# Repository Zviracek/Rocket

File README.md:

# Rocket
This repository contains everything needed for succesfull model-scale rocket flight. Or it should once it's done.

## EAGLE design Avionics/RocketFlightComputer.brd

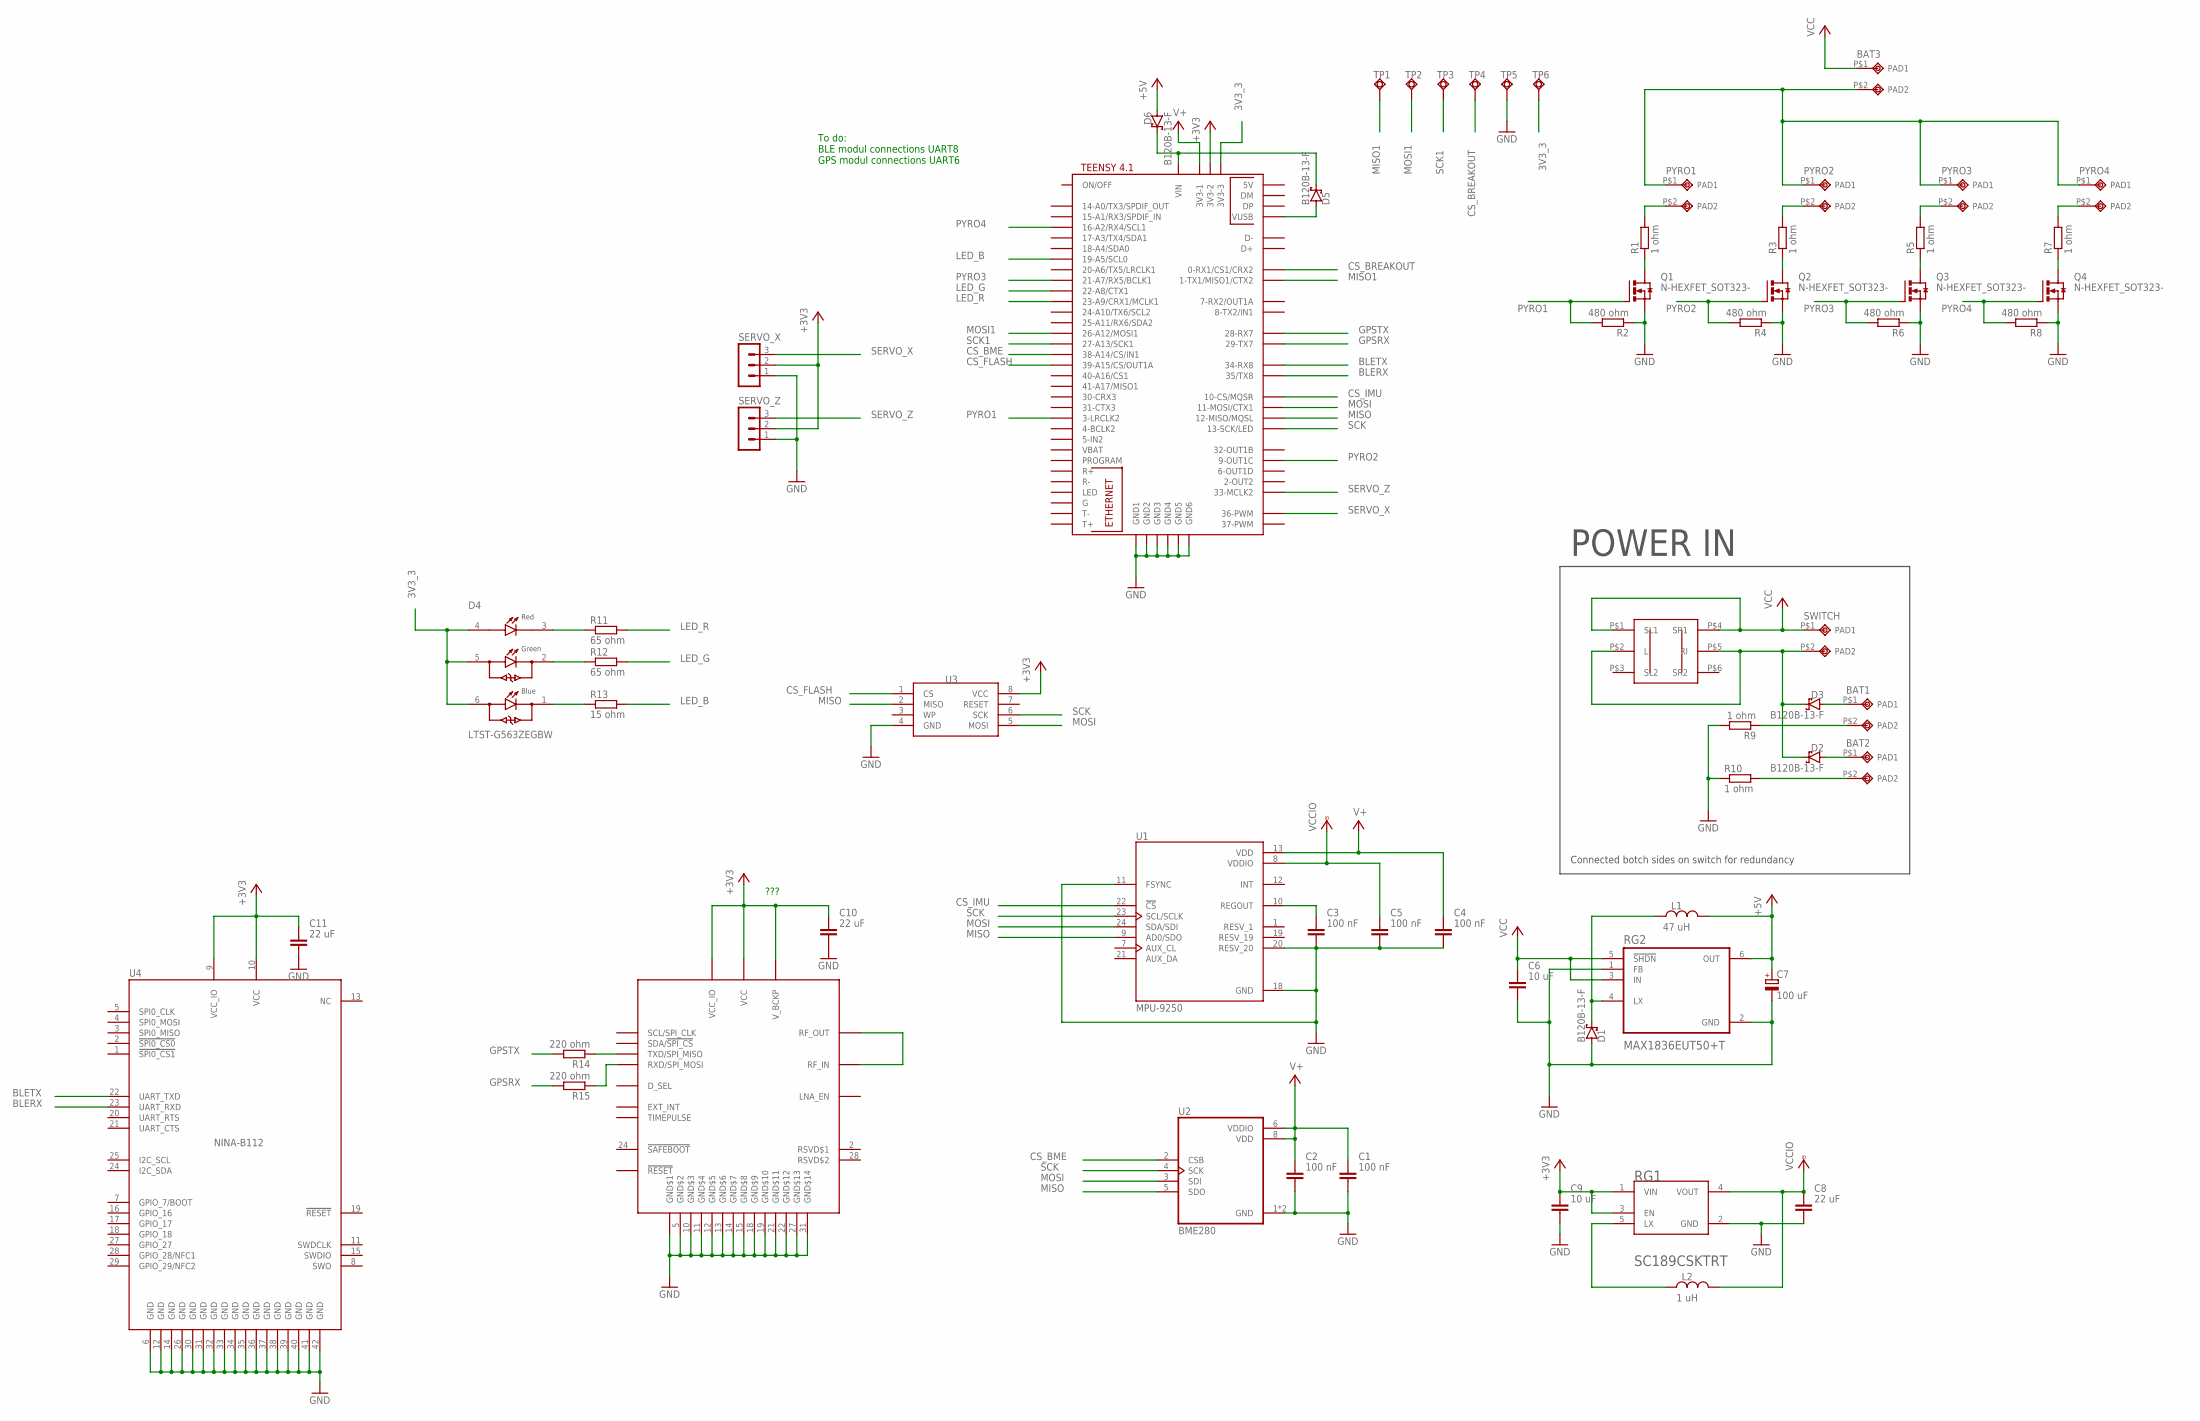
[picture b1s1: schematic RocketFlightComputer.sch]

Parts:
BAT1, BAT2, BAT3: 2PINPAD
C1, C2, C3, C4, C5: 100 nF; CAPC3216X135
C6, C9: 10 uF; CAPC3216X135
C7: 100 uF; B/3528-21W
C8, C10, C11: 22 uF; CAPC3216X135
D1, D2, D3, D5, D6: B120B-13-F; SMB
D4: LTST-G563ZEGBW; LED_LTST-G563ZEGBW
L1: 47 uH; INDM3225X240
L2: 1 uH; CAPC2012X110
PYRO1, PYRO2, PYRO3, PYRO4: 2PINPAD
Q1, Q2, Q3, Q4: N-HEXFET_SOT323-; SOT223
R1, R3, R5, R7, R9, R10: 1 ohm; R1206
R2, R4, R6, R8: 480 ohm; R1206
R11, R12: 65 ohm; R1206
R13: 15 ohm; R1206
R14, R15: 220 ohm; R1206
RG1: SEMTECH_SC189CSKTRTSEMTECH_SC189CSKTRT_0_0; SEMTECH_SC189CSKTRT_0
RG2: MAX1836EUT50+T; SOT95P280X145-6N
SERVO_X: MA03-1
SERVO_Z: MA03-1
SWITCH: 2PINPAD
TP1, TP2, TP3, TP4, TP5, TP6: TPSQTP13SQ; TP13SQ
U1: MPU-9250; QFN40P300X300X105-24N
U2: BME280; PSON65P250X250X100-8N
U3: FLASHSOIC8; SOIC127P600X175-8N
U4: NINA-B112; NINA112-42
U$1: TEENSY41
U$2: CAM-M8
U$3: DUAL_SW; DUAL_SWITCH

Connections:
3V3_3: D4.4, D4.5, D4.6, TP6.TP, U$1.3V3-3
+3V3: C9.1, C10.1, C11.1, RG1.1 (VIN), RG1.3 (EN), SERVO_X.2, SERVO_Z.2, U3.8 (VCC), U4.9 (VCC_IO), U4.10 (VCC), U$1.3V3-2, U$2.1 (VCC_IO), U$2.8 (V_BCKP), U$2.9 (VCC)
+5V: C7.+, D6.P$2 (A), L1.2, RG2.6 (OUT)
BLERX: U4.23 (UART_RXD), U$1.35-TX8 (35/TX8)
BLETX: U4.22 (UART_TXD), U$1.34-RX8
CS_BME: U2.2 (CSB), U$1.38-A14/CS/IN1
CS_BREAKOUT: TP4.TP, U$1.0-RX1/CS1/CRX2
CS_FLASH: U3.1 (CS), U$1.39-A15/CS/OUT1A
CS_IMU: U1.22 (!CS), U$1.10-CS\MQSR (10-CS/MQSR)
GND: C1.2, C2.2, C3.2, C4.2, C5.2, C6.2, C7.-, C8.2, C9.2, C10.2, C11.2, D1.P$2 (A), Q1.3 (S), Q2.3 (S), Q3.3 (S), Q4.3 (S), R2.1, R4.1, R6.1, R8.1, R9.2, R10.1, RG1.2 (GND), RG2.1 (FB), RG2.2 (GND), SERVO_X.1, SERVO_Z.1, TP5.TP, U1.11 (FSYNC), U1.18 (GND), U1.20 (RESV_20), U2.1 (GND), U2.7 (GND), U3.4 (GND), U4.6 (GND), U4.12 (GND), U4.14 (GND), U4.26 (GND), U4.30 (GND), U4.31 (GND), U4.32 (GND), U4.33 (GND), U4.34 (GND), U4.35 (GND), U4.36 (GND), U4.37 (GND), U4.38 (GND), U4.39 (GND), U4.40 (GND), U4.41 (GND), U4.42 (GND), U$1.GND1, U$1.GND2, U$1.GND3, U$1.GND4, U$1.GND5, U$1.GND6, U$2.4 (GND$1), U$2.5 (GND$2), U$2.10 (GND$3), U$2.11 (GND$4), U$2.12 (GND$5), U$2.13 (GND$6), U$2.14 (GND$7), U$2.15 (GND$8), U$2.18 (GND$9), U$2.19 (GND$10), U$2.21 (GND$11), U$2.22 (GND$12), U$2.27 (GND$13), U$2.31 (GND$14)
GPSRX: R15.2, U$1.29-TX7
GPSTX: R14.2, U$1.28-RX7
LED_B: R13.2, U$1.19-A5/SCL0
LED_G: R12.2, U$1.22-A8/CTX1
LED_R: R11.2, U$1.23-A9/CRX1/MCLK1
MISO: U1.9 (AD0/SDO), U2.5 (SDO), U3.2 (MISO), U$1.12-MISO/MQSL
MISO1: TP1.TP, U$1.1-TX1/MISO1/CTX2
MOSI: U1.24 (SDA/SDI), U2.3 (SDI), U3.5 (MOSI), U$1.11-MOSI/CTX1
MOSI1: TP2.TP, U$1.26-A12/MOSI1
unnamed: C3.1, U1.10 (REGOUT)
unnamed: D5.P$1 (B), D6.P$1 (B), U$1.VIN
unnamed: Q1.4 (D), R1.1
unnamed: PYRO1.P$2 (PAD2), R1.2
unnamed: Q2.4 (D), R3.1
unnamed: PYRO2.P$2 (PAD2), R3.2
unnamed: D2.P$1 (B), D3.P$1 (B), SWITCH.P$2 (PAD2), U$3.P$2 (LI), U$3.P$5 (RI)
unnamed: D4.3, R11.1
unnamed: Q3.4 (D), R5.1
unnamed: PYRO3.P$2 (PAD2), R5.2
unnamed: D4.2, R12.1
unnamed: Q4.4 (D), R7.1
unnamed: PYRO4.P$2 (PAD2), R7.2
unnamed: BAT1.P$2 (PAD2), R9.1
unnamed: BAT2.P$2 (PAD2), R10.2
unnamed: D4.1, R13.1
unnamed: D1.P$1 (B), L1.1, RG2.4 (LX)
unnamed: BAT2.P$1 (PAD1), D2.P$2 (A)
unnamed: BAT1.P$1 (PAD1), D3.P$2 (A)
unnamed: D5.P$2 (A), U$1.VUSB
unnamed: U$2.16 (RF_OUT), U$2.17 (RF_IN)
unnamed: L2.1, RG1.5 (LX)
unnamed: BAT3.P$2 (PAD2), PYRO1.P$1 (PAD1), PYRO2.P$1 (PAD1), PYRO3.P$1 (PAD1), PYRO4.P$1 (PAD1)
unnamed: R14.1, U$2.25 (TXD/SPI_MISO)
unnamed: R15.1, U$2.26 (RXD/SPI_MOSI)
PYRO1: Q1.1 (G), R2.2, U$1.3-LRCLK2
PYRO2: Q2.1 (G), R4.2, U$1.9-OUT1C
PYRO3: Q3.1 (G), R6.2, U$1.21-A7/RX5/BCLK1
PYRO4: Q4.1 (G), R8.2, U$1.16-A2/RX4/SCL1
SCK: U1.23 (SCL/SCLK), U2.4 (SCK), U3.6 (SCK), U$1.13-SCK/LED
SCK1: TP3.TP, U$1.27-A13/SCK1
SERVO_X: SERVO_X.3, U$1.36-PWM
SERVO_Z: SERVO_Z.3, U$1.33-MCLK2
V+: C1.1, C2.1, C4.1, U1.13 (VDD), U2.6 (VDDIO), U2.8 (VDD), U$1.3V3-1
VCC: BAT3.P$1 (PAD1), C6.1, RG2.3 (IN), RG2.5 (!SHDN), SWITCH.P$1 (PAD1), U$3.P$1 (SL1), U$3.P$4 (SR1)
VCCIO: C5.1, C8.1, L2.2, RG1.4 (VOUT), U1.8 (VDDIO)

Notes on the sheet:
Connected botch sides on switch for redundancy
POWER IN
To do: BLE modul connections UART8 GPS modul connections UART6
???

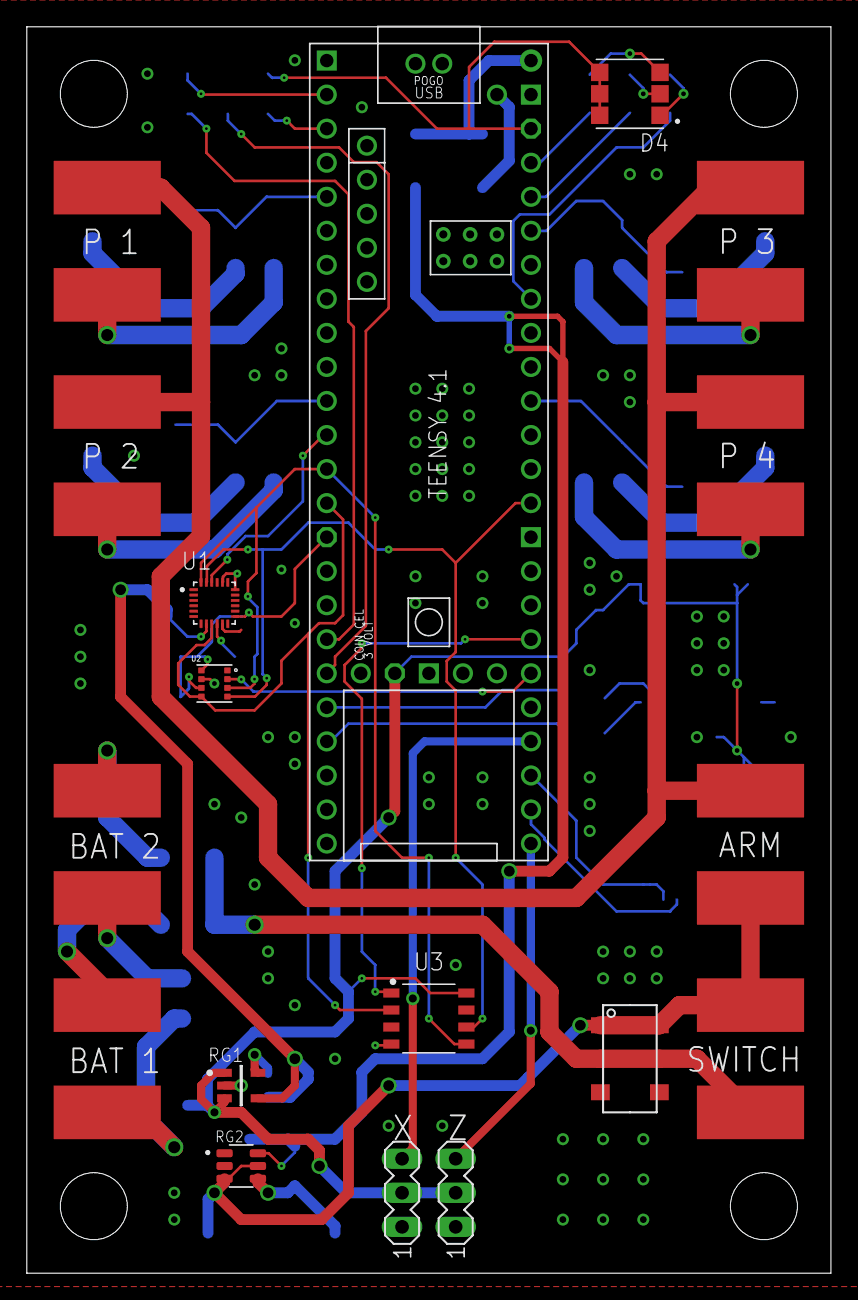
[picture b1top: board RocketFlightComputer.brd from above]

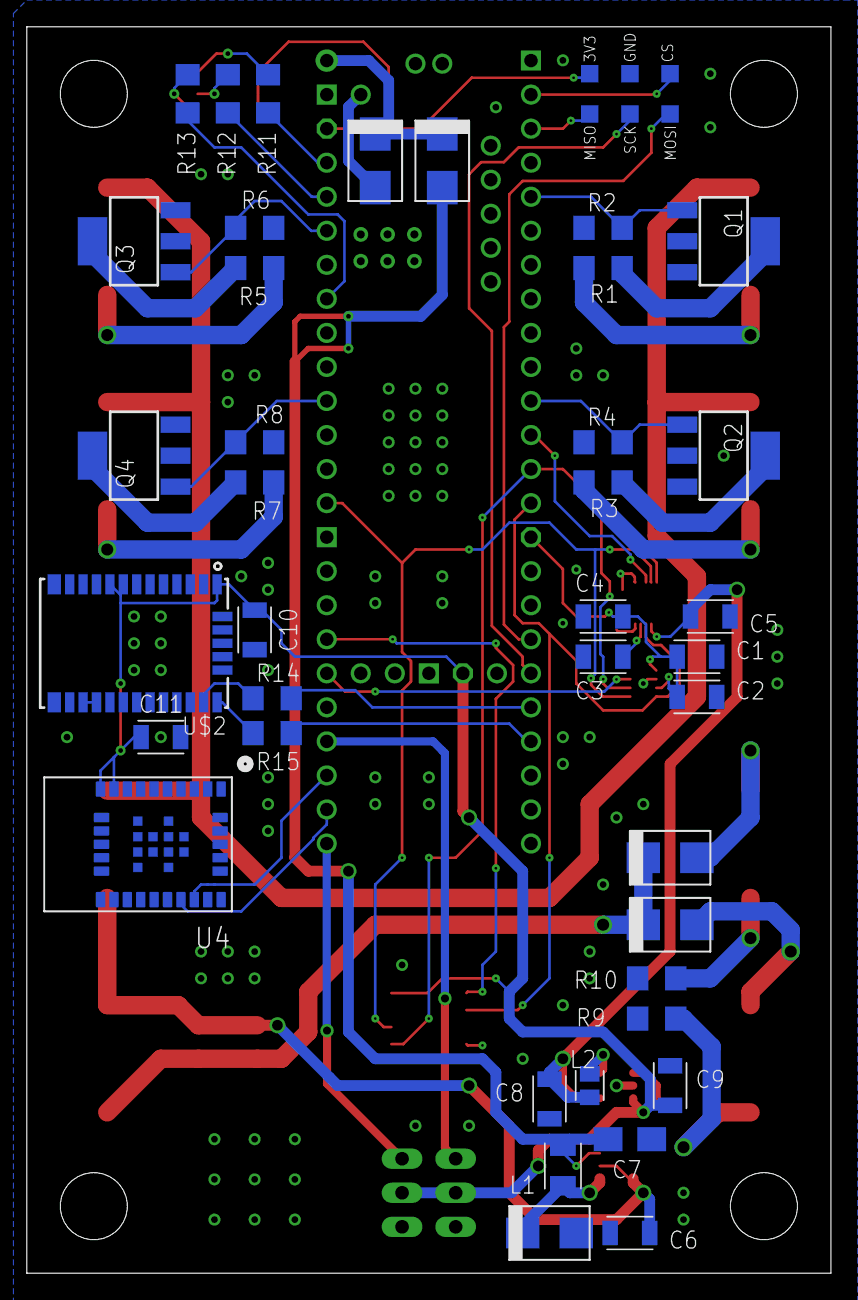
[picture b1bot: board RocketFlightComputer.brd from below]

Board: 2 copper layers, 60.0 x 93.0 mm, 63 parts (45 on the bottom side), 55 nets.

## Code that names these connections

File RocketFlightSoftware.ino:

//Servo control inclusion
#include <Servo.h>

//Comunication protocol inclusion
//#include "Wire.h" //Inclusion of wire.h is unnececarry because it's already included in MPU9250 library
#include <SPI.h>
#include <SoftwareSerial.h>

//IMU sensor inclusion
#include "quaternionFilters.h"
#include "MPU9250.h"

//SD card library inclusion
#include <SD.h>

//Macros for pins
#define LED_R 23
#define LED_G 22
#define LED_B 19

#define PYRO_1 3
#define PYRO_2 9
#define PYRO_3 21
#define PYRO_4 16

#define CS_FLASH 39
#define CS_IMU 10
#define CS_BME 38
#define CS_BREAKOUT 0

#define GPS_RX 29
#define GPS_TX 28

#define BL_RX 35
#define BL_TX 34

#define SERVO_X 36
#define SERVO_Z 33

//definiton of flight states
#define GroundIdle 1;
#define Countdown 2;
#define Launch 3;
#define Flight 4;
#define Return 5;
#define Landed 6;
#define LaunchAbort 7;
#define FlightAbort 8;

//FlightState global int
int flightState = GroundIdle;

//Base angle for servo
int targetAngleX = 90;
int targetAngleZ = 90;

//PID setup for servos
float ServoP = 10f, ServoI = 0.5f, ServoD = 0.5f;

float ServoXError, ServoZError;
float ServoXPID, ServoZPID;

//Time references for countdown
int countdownTimer = 120; //in seconds
int countdownEndTime;
int countdownTime;
int countdownHoldTime;
bool countdownPause = false;

//Macros and object for IMU I2C bus if external sensor is used, unactive when using onboard sensor!
#ifdef IMUI2C
  #define I2Cclock 400000
  #define I2Cport Wire
  #define MPU9250_ADDRESS MPU9250_ADDRESS_AD0 //I2C addres AD1 can also be used if needed

  //inicialization of IMU I2C object
  MPU9250 myIMU(MPU9250_ADDRESS, I2Cport, I2Cclock);
#else
//Macros and object for IMU SPI bus if onboard sensor is used
  //***Block for SPI IMU***
#endif

//Instances of servo objects
Servo servoX;
Servo servoZ;

//Instances of object using UART communication
SoftwareSerial bluetooth(BL_TX, BL_RX);
SoftwareSerial gps(GPS_TX, GPS_RX);


void setup() {
  //pin I/O setups
  pinMode(LED_R, OUTPUT);
  pinMode(LED_G, OUTPUT);
  pinMode(LED_B, OUTPUT);

  pinMode(PYRO_1, OUTPUT);
  pinMode(PYRO_2, OUTPUT);
  pinMode(PYRO_3, OUTPUT);
  pinMode(PYRO_4, OUTPUT);

  //servo setups
  servoX.attach(SERVO_X); 
  servoZ.attach(SERVO_Z); 

  //If using external IMU sensor inicilize I2C library
  #ifdef IMUI2C
    Wire.begin();

    //Read the WHO_AM_I register, this is a good test of communication
    byte c = myIMU.readByte(MPU9250_ADDRESS, WHO_AM_I_MPU9250);
    Serial.print(F("MPU9250 I AM 0x"));
    Serial.print(c, HEX);
    Serial.print(F(" I should be 0x"));
    Serial.println(0x71, HEX);
  #else
  //If using onboard IMU sensor inicilize SPI library
    //TODO: ***Block for SPI IMU***
  #endif

  Serial.begin(9600);
  bluetooth.begin();
  gps.begin();

  //Set servos at default angle
  servoX.write(targetAngleX);
  servoZ.write(targetAngleZ);
}

void loop()
  //Check for current state: GroundIdle, Countdown, Launch, Flight, Return, Landed, LaunchAbort, FlightAbort
  switch(flightState)
  {
    case 1: //Ground Idle - sensor logging directly to SD, wating for launch signal
      GroundIdleState();
      break;

    case 2: //Countdown - Countdown, SD card logging suspended, using FLASH instead
      CountdownState();
      break;

    case 3: //Launch - first few seconds of the flight checking for flight nominality, if launch is not detected, switch to LaunchAbort
      LaunchState();
      break;

    case 4: //Flight - stabilization online, complete loging, chechks for flight nominality or return state conditions, if flight is not nominal, switch to FlightAbort
      FlightState();
      break;

    case 5: //Return - MECO, deploy chutes at safe atitude, wait for landing
      ReturnState();
      break;

    case 6: //Landed - landing detected, transfer data from flash to SD
      LandedState();
      break;

    case 7: //LaunchAbort - error at countdown -> stop countdown, transfer data from flash to SD, add error log to SD
      LaunchAbortState();
      break;

    case 8: //FlightAbort - jiggle engine vector to bleed as much power as possible, extended logging to flash, special chute conditions, wait for landing
      FlightAbortState();
      break;  
  }
 
  //Pasive loops - IMU reading, reference reading and logging from GPS, Barometer and IMU
  #ifdef IMUI2C
    readIMUI2C();
  #else
    readIMUSPI();
  #endif
  
  //Servos PID
  ServoXError = targetAngleX - SERVO_X.read();
  ServoZError = targetAngleZ - SERVO_Z.read();

  targetAngleX = ServoXError;
  //Set servos ***I dont know where I should put it yet***
  writeServos(targetAngleX, targetAngleZ);
}

//Functions for each state
void GroundIdleState()
{
  //read bluetooth for launch signal
  byte DATA;
  if(bluetooth.available() > 0)
  {
    DATA = bluetooth.read();

    switch (DATA) 
    {
      case '1': //Start countdown
        flightState = Countdown;
        break;
    }
  
  }
}

void CountdownState()
{
  //time reference update
  countdownTime = countdownEndTime - millis();

  //TODO: send remaining time troughout bluetooth

  if(millis() => countdownEndTime) //countdown over, proceed to launch
  {
    flightState = Launch;
    //TODO: log this info to flash memory
  }

  //read bluetooth for launch abort signal
  //TODO: if bluetooth disconnects, we want to hold countdown
  byte DATA;
  if(bluetooth.available() > 0)
  {
    DATA = bluetooth.read();

    switch (DATA) 
    {
      case '0': //stop countdown, abort launch
        flightState = LaunchAbort;
        break;

      case '2': //skip countdown
        flightState = Launch;
        break;

      case '3': //pause countdown
        if(!countdownPause)
        {
          countdownHoldTime = countdownEndTime - millis();
          countdownPause = true;
        }
        countdownEndTime = millis() + 20000000; //Around 5 and half hour, should be enought :)
        break;

      case '4': //resume countdown
        if(countdownPause)
        {
          countdownEndTime = millis() + countdownHoldTime;
          countdownPause = false;
        }
        break;
    }
  
  }
}

void LaunchState()
{
  digitalWrite(PYRO_1, HIGH); //pyro_1 should always be first stage rocket motor

  //TODO: check if launch is nominal
  flightState = Flight;
}

void FlightState()
{
  digitalWrite(PYRO_1, LOW); //despite pyro charge should no longer condct, for safety reasons we want to switch pyro off

  if(false) //TODO: apogee condition
  {
    flightState = Return;
  }
}
 
void ReturnState()
{
  if(true) //TODO: altitude condition
  {
    digitalWrite(PYRO_3, HIGH);
  }

  if(false) //TODO: backup charge condition
  {
    digitalWrite(PYRO_4, HIGH);
  }
  
}

void LandedState()
{

}

void LaunchAbortState()
{

}

void FlightAbortState()
{

}

//Pasive loops functions
void readIMUI2C()
{

}

void readIMUSPI()
{

}

void writeServos(int angleX, int angleZ)
{
  oldAngleX = servoX.read();
  oldAngleZ = servoZ.read();

  if(oldAngleX != angleX)
  {
    servoX.write(angleX);
  }

  if(oldAngleZ != angleZ)
  {
    servoZ.write(angleZ);
  }
}
